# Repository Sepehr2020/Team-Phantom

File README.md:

This repository includes some of the projects and/or tutorials that I have either worked on, learned from more experiecned students or tought them to newere Team Phantom members.

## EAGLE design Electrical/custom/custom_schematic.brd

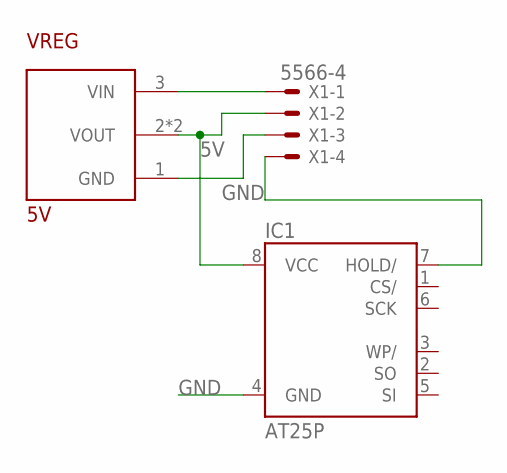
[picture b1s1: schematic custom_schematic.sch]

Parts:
IC1: AT25P; DIL08
VREG: 5V; VOLTAGE-REGULATOR
X1: 5566-4

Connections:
5V: IC1.8 (VCC), VREG.2 (VOUT), VREG.2B (VOUT), X1.2
GND: IC1.4 (GND), VREG.1 (GND), X1.3
unnamed: VREG.3 (VIN), X1.1
unnamed: IC1.7 (HOLD/), X1.4

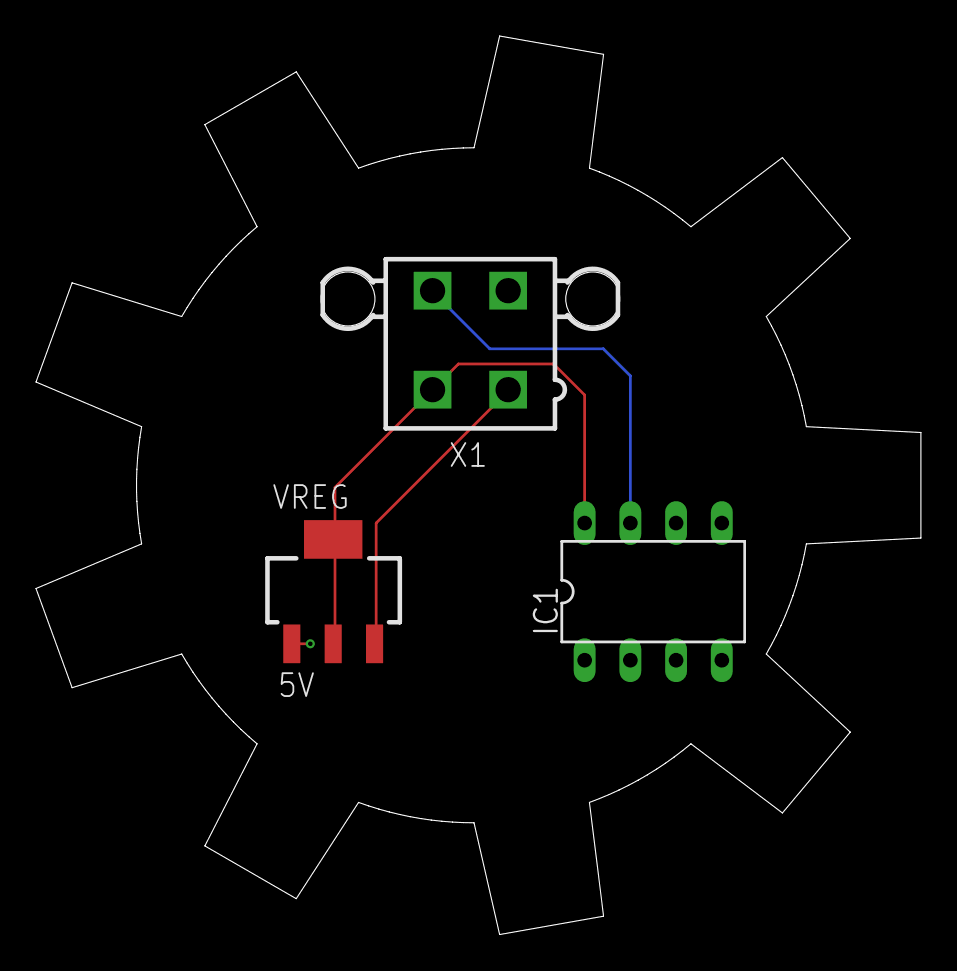
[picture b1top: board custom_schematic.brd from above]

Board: 2 copper layers, 49.2 x 49.9 mm, 3 parts (0 on the bottom side), 4 nets.
